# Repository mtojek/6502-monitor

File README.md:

# Monitor 6502 microprocessor with Arduino UNO R3 and custom input extension

This repository contains Kicad schematics and .ino source files to extend your Arduino UNO R3 with additional inputs. If you are following the Ben's Eater course to [build a 6502 computer](https://eater.net/6502), you will see that Ben operates on Arduino MEGA. Use schematics and source code from this repository to continue the Ben's course with Arduino UNO.

The 6502 monitor is programmed to observe address and data buses, and the read/write mode. For debugging and learning purposes, it's advised to use the external clock signal.

## Sample output

Check Arduino serial monitor to preview buses:

```
<address> <data> <address_hex> <Read/Write mode> <data_hex>
0000000110010110 00000000    0196 R 00
1111111111111100 00000000    fffc R 00
1111111111111101 00000000    fffd R 00
0000000000000000 00000000    0000 R 00
0000000000000001 00000000    0001 R 00
0000000110010101 00000000    0195 W 00
0000000110010100 00000010    0194 W 02
0000000110010011 00000110    0193 W 06
1111111111111110 00000000    fffe R 00
1111111111111111 00000000    ffff R 00
0011000000110000 00000000    3030 R 00
0011000000110001 00000000    3031 R 00
0011000000110010 00000000    3032 R 00
0011000000110011 00000000    3033 R 00
0011000000110100 00000000    3034 R 00
0011000000110101 00000000    3035 R 00
```

## Kicad preview

## Photos

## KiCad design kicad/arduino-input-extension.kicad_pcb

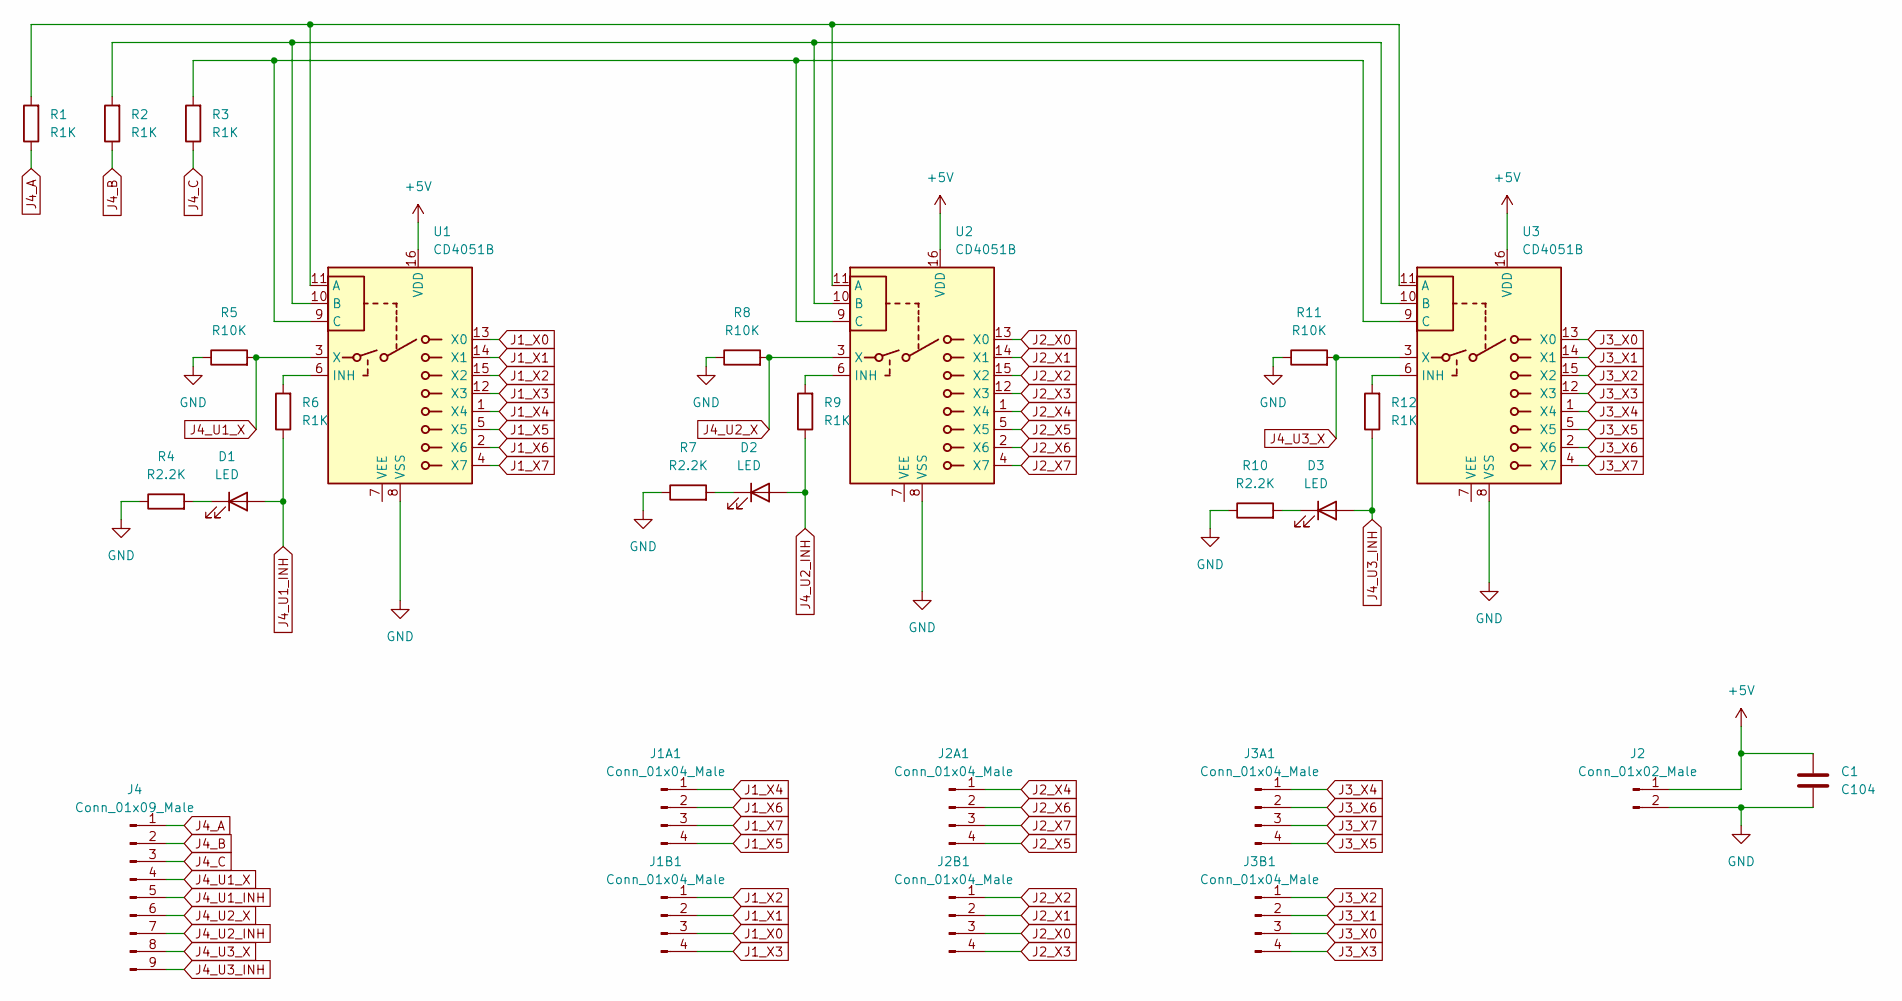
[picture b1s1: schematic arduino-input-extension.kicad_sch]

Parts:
C1: C104; C_Disc_D7.5mm_W4.4mm_P5.00mm
D1, D2, D3: LED; LED_D5.0mm
J1A1, J1B1, J2A1, J2B1, J3A1, J3B1: Conn_01x04_Male; PinHeader_1x04_P2.54mm_Vertical
J2: Conn_01x02_Male; PinHeader_1x02_P2.54mm_Vertical
J4: Conn_01x09_Male; PinHeader_1x09_P2.54mm_Vertical
R1, R2, R3, R6, R9, R12: R1K; R_Axial_DIN0207_L6.3mm_D2.5mm_P10.16mm_Horizontal
R4, R7, R10: R2.2K; R_Axial_DIN0207_L6.3mm_D2.5mm_P10.16mm_Horizontal
R5, R8, R11: R10K; R_Axial_DIN0207_L6.3mm_D2.5mm_P10.16mm_Horizontal
U1, U2, U3: CD4051B; DIP-16_W7.62mm_Socket_LongPads

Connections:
+5V: C1.1, J2.1, U1.16 (VDD), U2.16 (VDD), U3.16 (VDD)
GND: C1.2, J2.2, R4.1, R5.1, R7.1, R8.1, R10.1, R11.1, U1.8 (VSS), U2.8 (VSS), U3.8 (VSS)
J1_X0: J1B1.3, U1.13 (X0)
J1_X1: J1B1.2, U1.14 (X1)
J1_X2: J1B1.1, U1.15 (X2)
J1_X3: J1B1.4, U1.12 (X3)
J1_X4: J1A1.1, U1.1 (X4)
J1_X5: J1A1.4, U1.5 (X5)
J1_X6: J1A1.2, U1.2 (X6)
J1_X7: J1A1.3, U1.4 (X7)
J2_X0: J2B1.3, U2.13 (X0)
J2_X1: J2B1.2, U2.14 (X1)
J2_X2: J2B1.1, U2.15 (X2)
J2_X3: J2B1.4, U2.12 (X3)
J2_X4: J2A1.1, U2.1 (X4)
J2_X5: J2A1.4, U2.5 (X5)
J2_X6: J2A1.2, U2.2 (X6)
J2_X7: J2A1.3, U2.4 (X7)
J3_X0: J3B1.3, U3.13 (X0)
J3_X1: J3B1.2, U3.14 (X1)
J3_X2: J3B1.1, U3.15 (X2)
J3_X3: J3B1.4, U3.12 (X3)
J3_X4: J3A1.1, U3.1 (X4)
J3_X5: J3A1.4, U3.5 (X5)
J3_X6: J3A1.2, U3.2 (X6)
J3_X7: J3A1.3, U3.4 (X7)
J4_A: J4.1, R1.1
J4_B: J4.2, R2.1
J4_C: J4.3, R3.1
J4_U1_INH: D1.2 (A), J4.5, R6.1
J4_U1_X: J4.4, R5.2, U1.3 (X)
J4_U2_INH: D2.2 (A), J4.7, R9.1
J4_U2_X: J4.6, R8.2, U2.3 (X)
J4_U3_INH: D3.2 (A), J4.9, R12.1
J4_U3_X: J4.8, R11.2, U3.3 (X)
unnamed: D1.1 (K), R4.2
unnamed: D2.1 (K), R7.2
unnamed: D3.1 (K), R10.2
unnamed: R1.2, U1.11 (A), U2.11 (A), U3.11 (A)
unnamed: R2.2, U1.10 (B), U2.10 (B), U3.10 (B)
unnamed: R3.2, U1.9 (C), U2.9 (C), U3.9 (C)
unnamed: R6.2, U1.6 (INH)
unnamed: R9.2, U2.6 (INH)
unnamed: R12.2, U3.6 (INH)

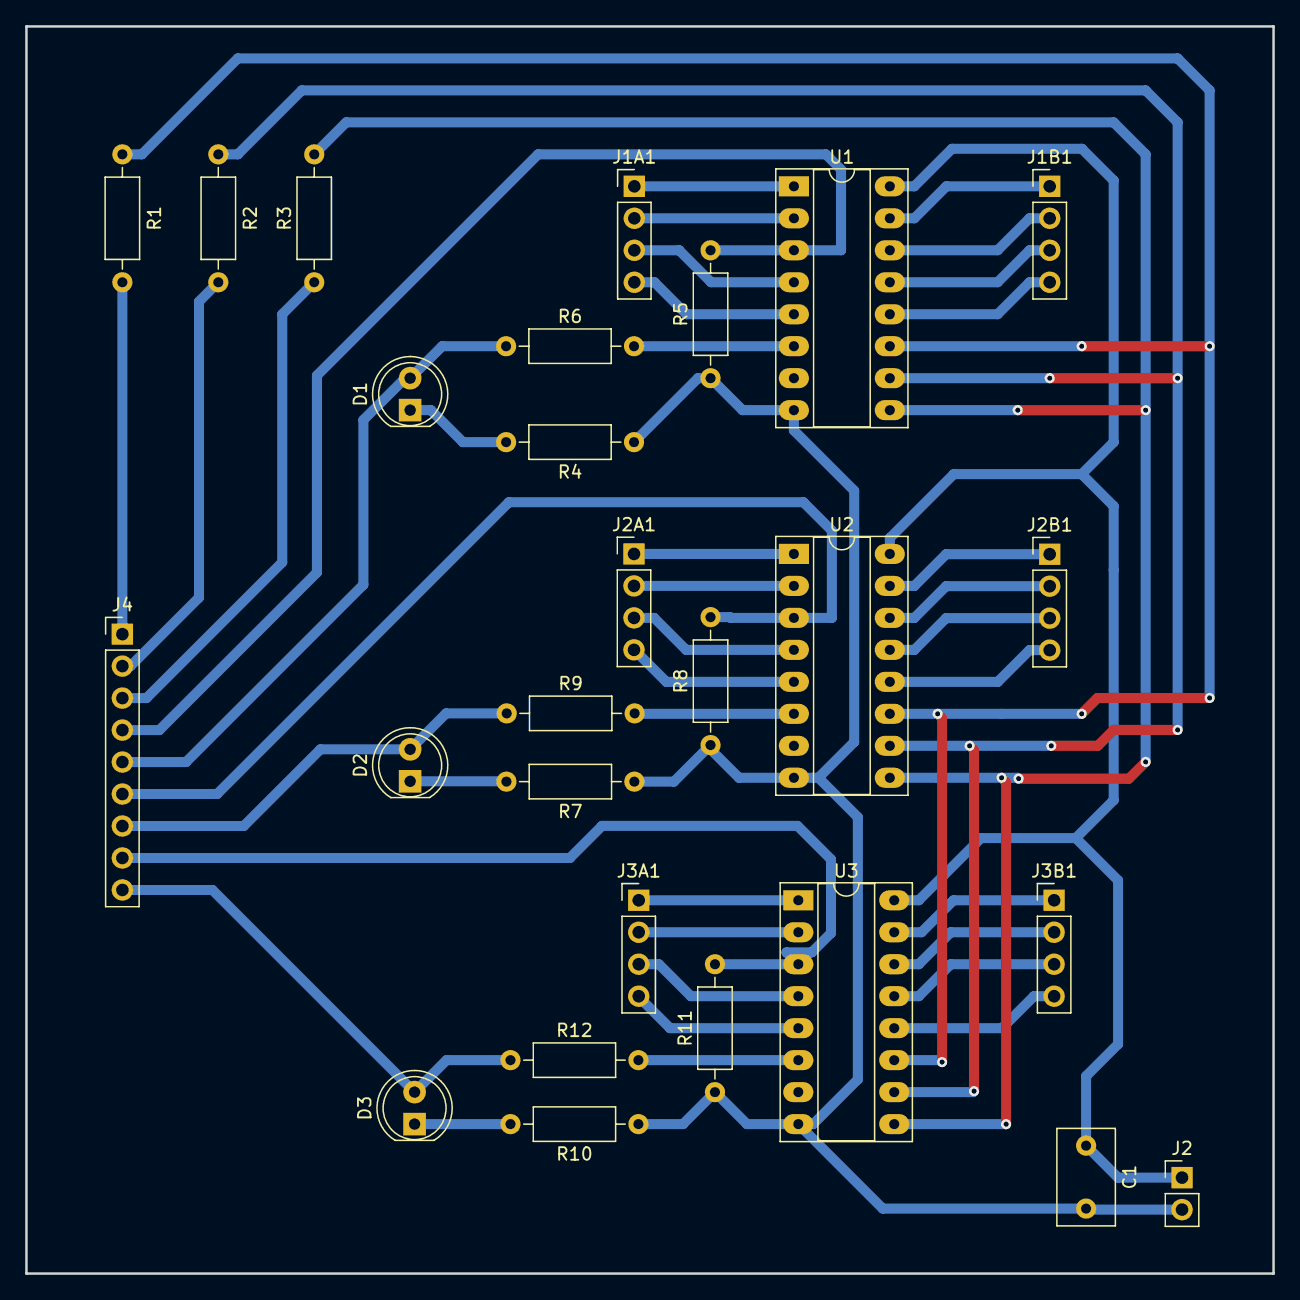
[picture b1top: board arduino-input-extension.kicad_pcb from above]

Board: 2 copper layers, 99.1 x 99.1 mm, 27 parts (0 on the bottom side), 44 nets.

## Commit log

2022-02-08 Bootstrap for 6502 monitor
2022-02-08 Pretty printer
2022-02-08 PinState
2022-02-08 Rename to readPins
2022-02-09 Input Extension works without pin ordering
2022-02-09 Map pins to real order
2022-02-09 Comment
2022-02-09 Format code
2022-02-10 Fix: reading pins
2022-02-11 Attach to clock interrupt
2022-02-13 Print buses
2022-02-13 PCB design
2022-02-13 Fix: gitignore
2022-02-13 Screenshots
2022-02-13 Add photos
2022-02-13 Add datasheets
2022-02-13 Resize graphics
2022-03-27 Trigger on FALLING
